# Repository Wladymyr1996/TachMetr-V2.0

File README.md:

# TachMetr-V2.0
The is a LED tachometer for my trike. Work on Atmega8A_AU and MAX7219.

Author: Stadnyk Volodymyr.

Name: TachMetr V2.0.		

License: Free for all.	

KiCad project in folder "Tachmetr V2".

KiCad проект в теці "Tachmetr V2".

KiCad проект в папке "Tachmetr V2".

For compile the firmware for Atmega8, you can run "make".

Для побудови прошивки для Atmega8, Ви можете запустити "make".

Для постройки прошивки для Atmega8, Вы можете запустить "make".

If you have any questions about this project, you can contact with me in Telegram https://t.me/Wladymyr .

Якщо Ви маєте питання щодо цього проекту, Ви можете зв'язатися зі мною в Телеграмі https://t.me/Wladymyr .

Если Вы имеете впоросы по поводу этого проекта, Вы можете свзаться со мной в Телеграме https://t.me/Wladymyr .

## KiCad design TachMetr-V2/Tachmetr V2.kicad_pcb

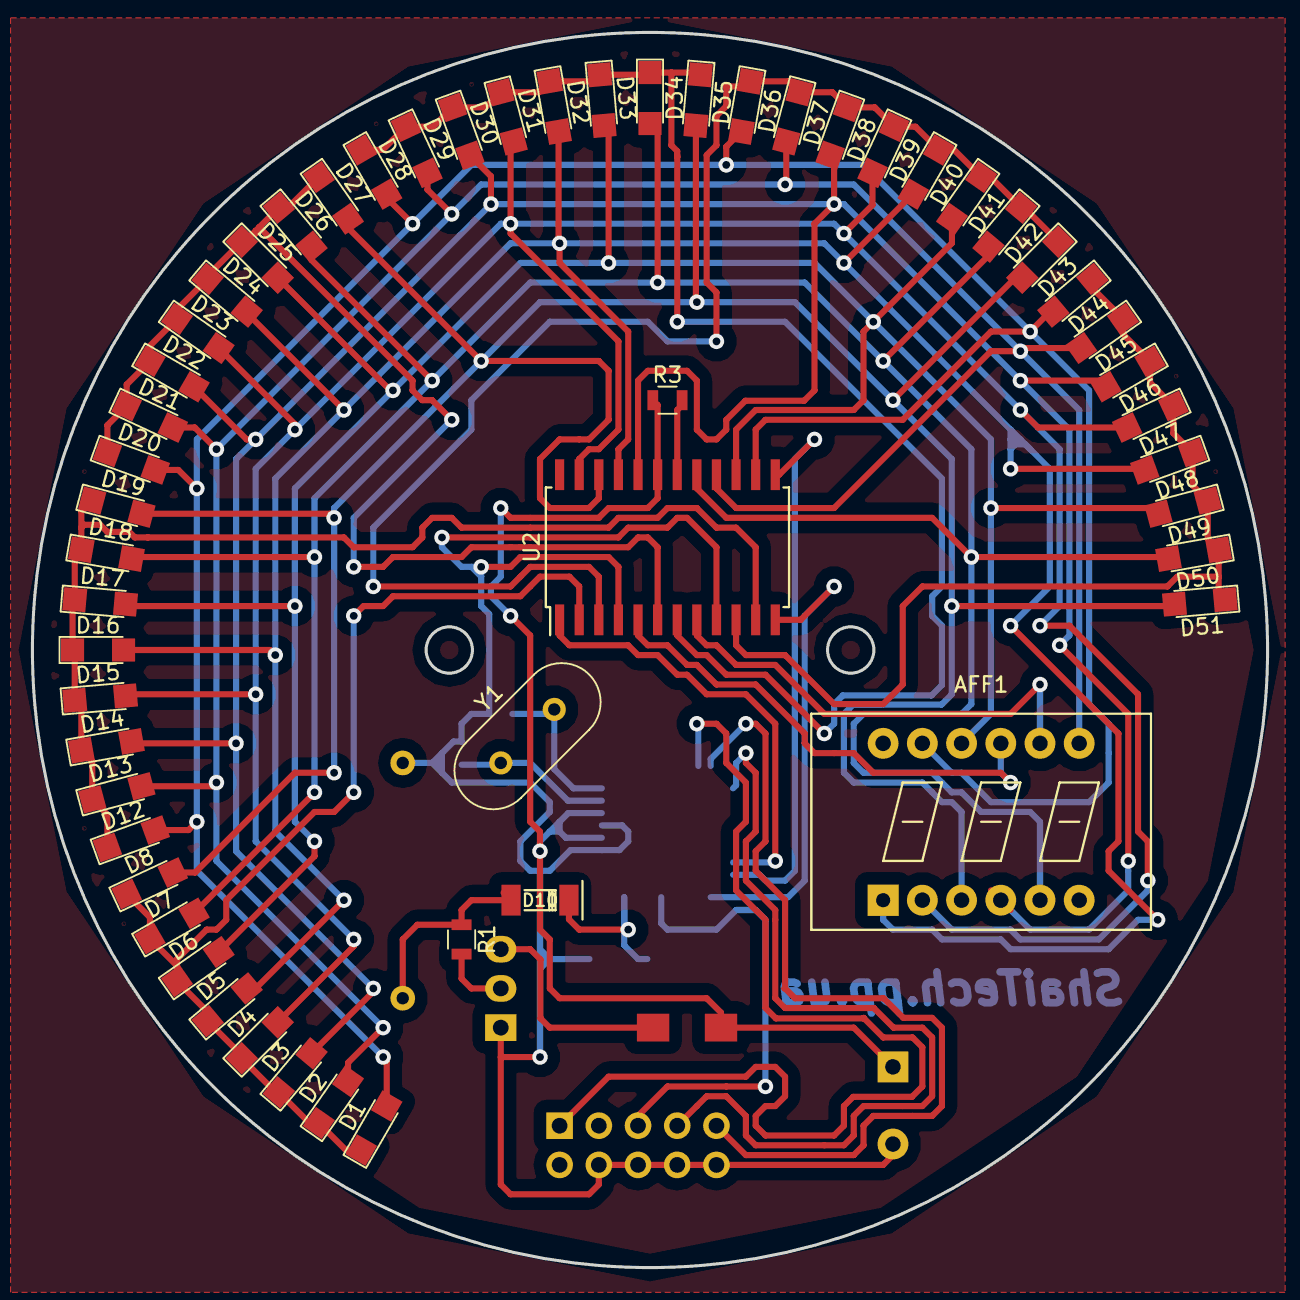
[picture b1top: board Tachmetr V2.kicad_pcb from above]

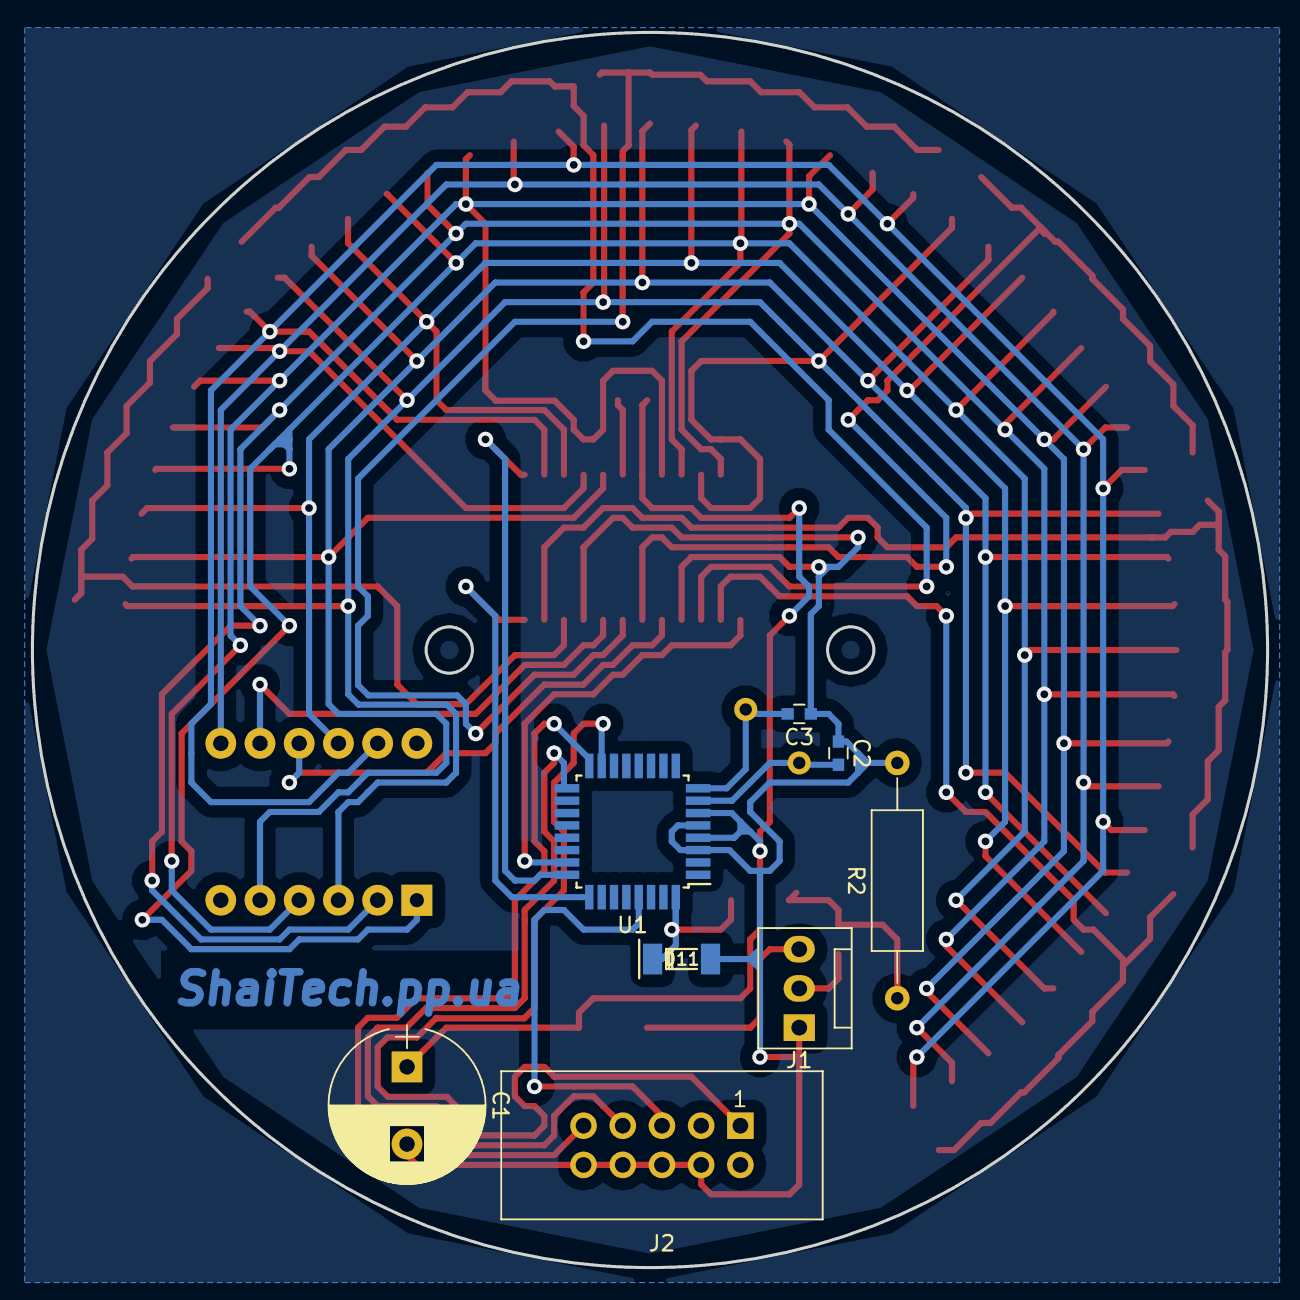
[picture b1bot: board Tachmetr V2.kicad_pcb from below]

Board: 2 copper layers, 80.0 x 80.0 mm, 63 parts (8 on the bottom side), 32 nets.

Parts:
AFF1: CC56-12; Cx56-12
C1: 1000uF; CP_Radial_D10.0mm_P5.00mm
C2, C3: 22pF; C_0603
D1, D2, D3, D4, D5, D6, D7, D8, D12, D13, D14, D15, D16, D17, D18, D19, D20, D21, D22, D23, D24, D25, D26, D27, D28, D29, D30, D31, D32, D33, D34, D35, D36, D37, D38, D39, D40, D41, D42, D43, D44, D45, D46, D47, D48, D49, D50, D51: LED; LED_1206
D9: M7; DO-214AC
D10: 4148; SOD-80
D11: C5V1; SOD-80
J1: CONN_01X03; Fan_Pin_Header_Straight_1x03
J2: USBASP; IDC_Header_Straight_10pins
R1: 5K1; R_0805
R2: 2K; R_Axial_DIN0309_L9.0mm_D3.2mm_P15.24mm_Horizontal
R3: 10K; R_0805
U1: ATMEGA8A-AU; TQFP-32_7x7mm_Pitch0.8mm
U2: MAX7219; SOIC-24W_7.5x15.4mm_Pitch1.27mm
Y1: 12MHz; Crystal_HC18-U_Vertical

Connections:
+5V: C1.1, D9.1, R3.1, U1.4, U1.6, U2.19
/CLK: U1.24, U2.13
/DATA: U1.23, U2.1
/DIG0: D1.1, D2.1, D3.1, D4.1, D5.1, D6.1, D7.1, D8.1, U2.2
/DIG1: D12.1, D13.1, D14.1, D15.1, D16.1, D17.1, D18.1, D19.1, U2.11
/DIG2: D20.1, D21.1, D22.1, D23.1, D24.1, D25.1, D26.1, D27.1, U2.6
/DIG3: D28.1, D29.1, D30.1, D31.1, D32.1, D33.1, D34.1, D35.1, U2.7
/DIG4: D36.1, D37.1, D38.1, D39.1, D40.1, D41.1, D42.1, D43.1, U2.3
/DIG5: D44.1, D45.1, D46.1, D47.1, D48.1, D49.1, D50.1, D51.1, U2.10
/DIG6: AFF1.9, U2.5
/DIG7: AFF1.8, U2.8
/LOAD: U1.25, U2.12
/SEGA: AFF1.11, D1.2, D12.2, D20.2, D28.2, D36.2, D44.2, U2.14
/SEGB: AFF1.7, D2.2, D13.2, D21.2, D29.2, D37.2, D45.2, U2.16
/SEGC: AFF1.4, D3.2, D14.2, D22.2, D30.2, D38.2, D46.2, U2.20
/SEGD: AFF1.2, D4.2, D15.2, D23.2, D31.2, D39.2, D47.2, U2.23
/SEGDP: AFF1.3, D8.2, D19.2, D27.2, D35.2, D43.2, D51.2, U2.22
/SEGE: AFF1.1, D5.2, D16.2, D24.2, D32.2, D40.2, D48.2, U2.21
/SEGF: AFF1.10, D6.2, D17.2, D25.2, D33.2, D41.2, D49.2, U2.15
/SEGG: AFF1.5, D7.2, D18.2, D26.2, D34.2, D42.2, D50.2, U2.17
GND: C1.2, C2.1, C3.1, D11.2, J1.1, J2.4, J2.6, J2.8, J2.10, R2.2, U1.3, U1.5, U2.4, U2.9
IN: J1.2, R1.2
IN_5V: D10.1, D11.1, U1.32
MISO: J2.9, U1.16
MOSI: J2.1, U1.15
unnamed: C2.2, U1.7, Y1.1
unnamed: C3.2, U1.8, Y1.2
unnamed: D9.2, J1.3
unnamed: D10.2, R1.1, R2.1
unnamed: R3.2, U2.18
RESET: J2.5, U1.29
SCK: J2.7, U1.17
